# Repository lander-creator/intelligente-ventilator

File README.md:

# intelligente-ventilator
Sensors: LM335; BMP2080

De bedoeling is van een ventilatorsturing te bouwen die voorkomt dat de compressor van een inbouw ijskastje oververhit geraakt.  We maken hiervoor gebruik van een analoge sensor LM335.
Bij kamertemperatuur doet hij niks, maar wanneer de ruimte in de keukenkast oploopt gaat hij vanaf 25 graden langzaam beginnen te draaien (PWM) proportioneel tot bij een temperatuur van 40 graden waar hij 100 procent draait.
De werking wordt met een RGB LED weergeven.

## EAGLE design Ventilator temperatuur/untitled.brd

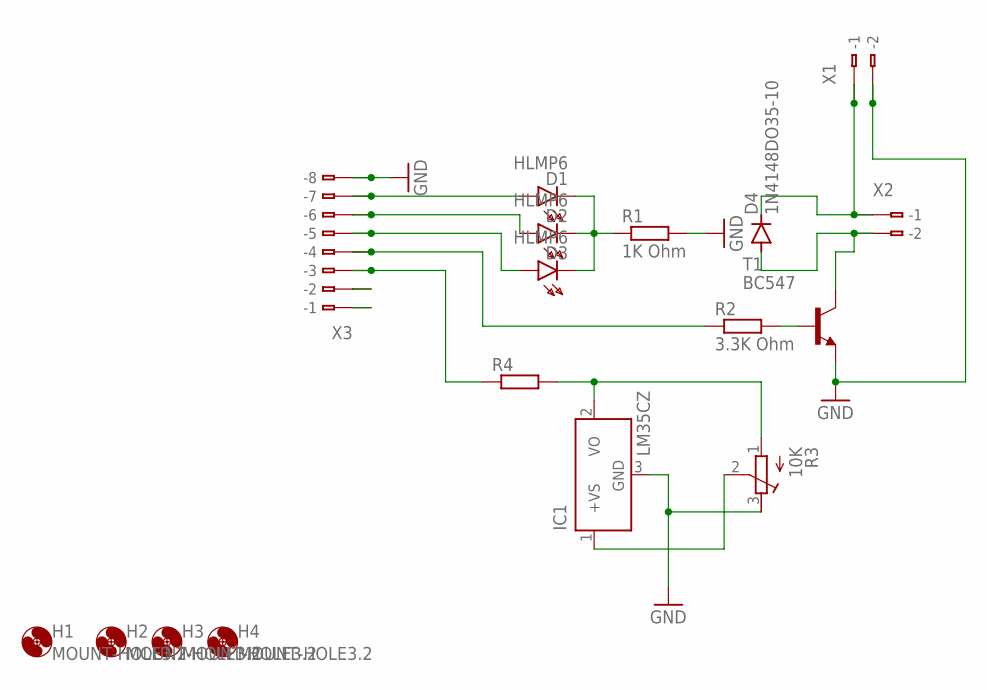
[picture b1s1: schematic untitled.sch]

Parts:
D1, D2, D3: HLMP6
D4: 1N4148DO35-10; DO35-10
H1, H2, H3, H4: MOUNT-HOLE3.2; 3,2
IC1: LM35CZ; TO92
R1: 1K Ohm; 0411/15
R2: 3.3K Ohm; 0411/15
R3: 10K; RTRIM3296X
R4: R-EU_0411/15; 0411/15
T1: BC547; TO92
X1, X2: 233-102
X3: 233-108

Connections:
GND: IC1.3 (GND), R1.2, R3.3 (E), T1.1 (E), X1.A2 (-2), X1.B2 (B-2), X3.A8 (-8), X3.B8 (B-8)
unnamed: IC1.1 (+VS), R3.2 (S)
unnamed: D4.A, T1.3 (C), X2.A2 (-2), X2.B2 (B-2)
unnamed: D1.A, X3.A7 (-7), X3.B7 (B-7)
unnamed: R2.2, T1.2 (B)
unnamed: R2.1, X3.A4 (-4), X3.B4 (B-4)
unnamed: D1.K, D2.K, D3.K, R1.1
unnamed: D2.A, X3.A6 (-6), X3.B6 (B-6)
unnamed: D3.A, X3.A5 (-5), X3.B5 (B-5)
unnamed: D4.C, X1.A1 (-1), X1.B1 (B-1), X2.A1 (-1), X2.B1 (B-1)
unnamed: IC1.2 (VO), R3.1 (A), R4.2
unnamed: X3.A2 (-2), X3.B2 (B-2)
unnamed: R4.1, X3.A3 (-3), X3.B3 (B-3)
unnamed: X3.A1 (-1), X3.B1 (B-1)

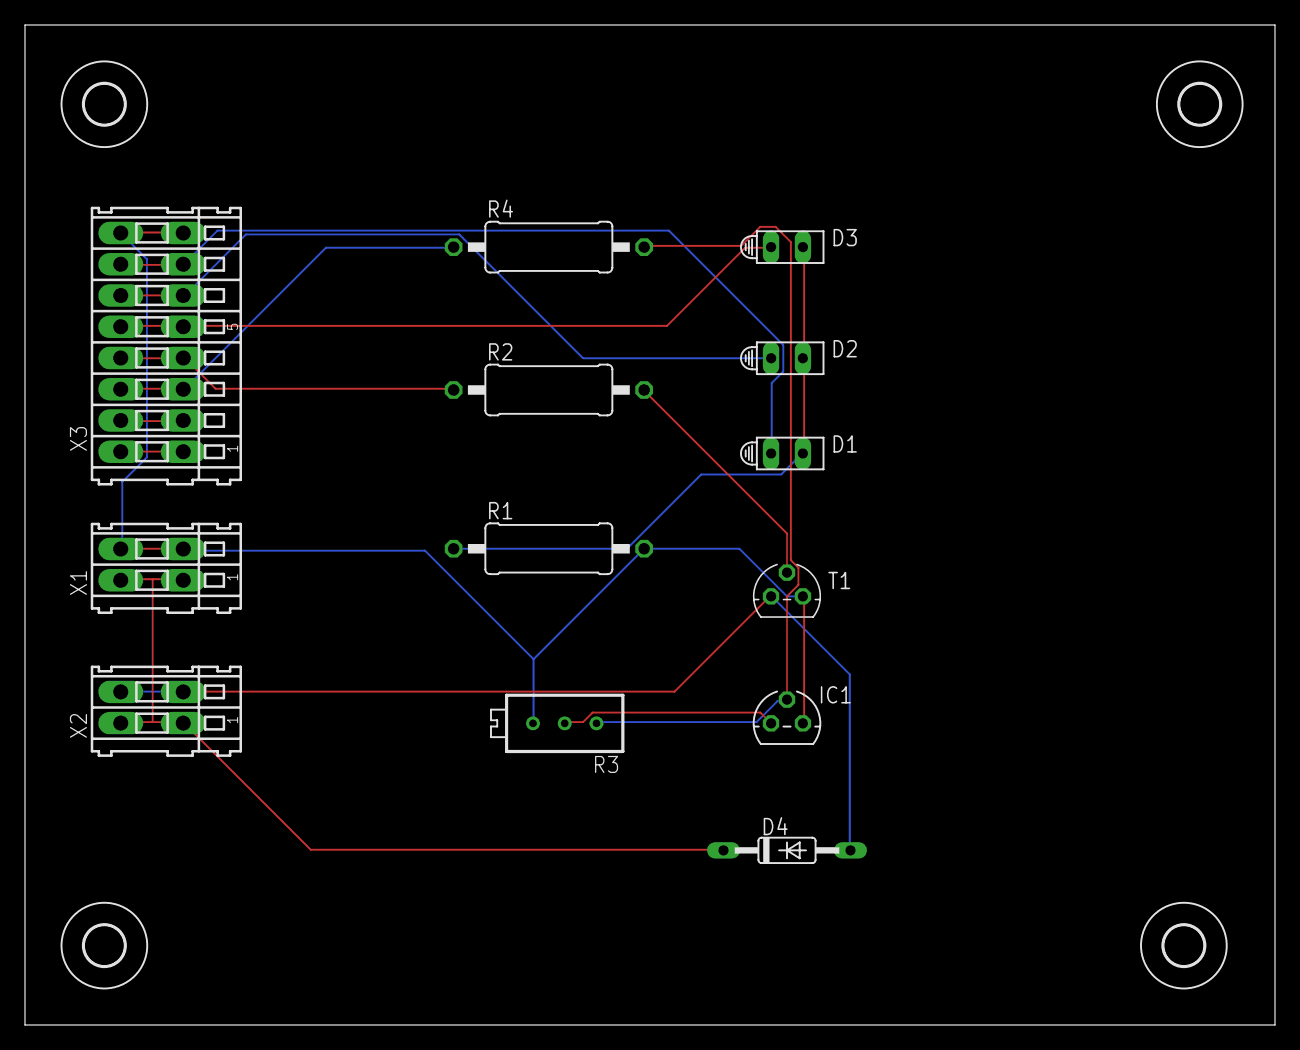
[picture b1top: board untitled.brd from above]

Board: 2 copper layers, 100.0 x 80.0 mm, 17 parts (0 on the bottom side), 14 nets.
